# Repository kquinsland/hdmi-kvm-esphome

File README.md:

# `uart_kvm` custom component for ESPHome

This custom component allows for basic control over a generic 8:1 HDMI2.0 KVM switch.
Specifically developed for model number [`PX-UHDKVM801-2.0`](https://www.aliexpress.com/item/1005003927404402.html).

Photos of the internals can be found [on my personal site](https://karlquinsland.com/hdmi-kvm-teardown-and-esphome/).

## Using the component

**Note:** It is possible to get _basic_ control over the KVM without this custom component! ESPHome has _native_ support for _writing_ to a UART. If you only need to tell the KVM what to do then you can use the native [`uart.write`](https://esphome.io/components/uart.html#uart-write-action) call!

However, if  you also want to probe the KVM to get the current active input bank, you will need to _read_ from the UART which can't be done with the native UART component. That's where this custom component comes into play :).

To load this custom component in your ESPHome configuration, you need to use the [`external_components`](https://esphome.io/components/external_components.html) block like so:

```yaml
external_components:
  - source:
      type: git
      url: https://github.com/kquinsland/hdmi-kvm-esphome
    components: [ uart_kvm ]
```

If you have any issues, try to remove the local cache:

```shell
$ rm -rf .esphome/external_components
```

## Example YAML:

This is not a _complete_ YAML file for ESPHome but it does illustrate how to use the custom component and to control the KVM directly with `uart.write` for the various functionalities that the custom component does NOT implement:

```yaml
esphome:
  on_boot:
    priority: 600
    then:
      # Buzzer on is helpful for testing and to know when an automation triggers a change
      - switch.turn_on: sw_tmpl_buzzer
      # I do not want the KVM to automatically switch to any new active HDMI cable
      - switch.turn_off: sw_tmpl_auto_input

# See: https://esphome.io/components/external_components.html
# Will be cached in .esphome/external_components/
##
external_components:
  - source:
      type: git
      url: https://github.com/kquinsland/hdmi-kvm-esphome
    components: [ uart_kvm ]

##
# Expose a dropdown/select to the user via HA
# See: https://esphome.io/components/select/template.html
##
select:
  - platform: template
    id: tmpl_sel_active_port
    name: "Active Bank"
    optimistic: false
    # Create one option for each host the KVM is to control
    # You can use any string you like but the `set_active_bank()` requires an `int` so
    #   choose the strings in the select wisely!
    # Create an entry for each input bank you wish to be able to switch between.
    # E.G.: If you only have 5 hosts attached to an 8 bank switch, you can safely
    #   leave options for 6,7,8 off.
    # In testing the KVM silently ignores commands to switch to an input bank beyond
    #   what the switch supports. E.G.: telling an 8 port KVM to make bank 10 active 
    #    does nothing.
    ##
    options:
      - "1"
      - "2"
      - "3"
      - "4"
      - "5"
      - "6"
      - "7"
      - "8"
    set_action:
      then:
        lambda: |-
          // ESPHome/HA use strings in select components. atoi() fixes this for us :)
          int bank = atoi(x.c_str());
          id(kvm1).set_active_bank(bank);
    # We poll the uart to get the current port
    # Note: ESPHome polls get_active_bank() every several seconds. Unless we actively tell ESPHome to
    #   re-run this lambda as soon as the KVM active input bank changes, this value will lag behind reality
    lambda: |-
      int active = id(kvm1).get_active_bank();
      return to_string(active);

# The initial documentation that the seller provided did not define a way to inquire about buzzer active state or active input chase behavior so we can implement this with standard `uart.write` rather than in custom c++
switch:
  - platform: template
    id: sw_tmpl_buzzer
    name: "${friendly_name_short} Buzzer"
    icon: "mdi:bullhorn"
    entity_category: "config"
    device_class: "switch"
    optimistic: True
    # I don't know how to confirm the state of things so we must assume that sending the "off" command will be enough to turn it off. In testing, sending the "off" command is reliable.
    # If this was not the case, then we could change how things work in HA: instead of a switch
    #   the user will see 2 buttons: one for on, the other for off.
    assumed_state: false
    turn_on_action:
        # Note: the KVM does a short chirp to indicate that it is on
      - uart.write: [0xAA, 0xBB, 0x03, 0x02, 0x01, 0xEE]
    turn_off_action:
      - uart.write: [0xAA, 0xBB, 0x03, 0x02, 0x00, 0xEE]

  - platform: template
    id: sw_tmpl_auto_input
    name: "${friendly_name_short} Auto Input Detection"
    icon: "mdi:bullhorn"
    entity_category: "config"
    device_class: "switch"
    optimistic: True
    assumed_state: False
    turn_on_action:
      - uart.write: [0xAA, 0xBB, 0x03, 0x81, 0x01, 0xEE]
    turn_off_action:
      - uart.write: [0xAA, 0xBB, 0x03, 0x81, 0x00, 0xEE]

uart:
  # We want to impersonate the remote/handset by injecting via the HTX pin which is mapped to 17
  tx_pin: GPIO17
  # Likewise, if the motor controller sends anything to the remote, we _also_ want to hear it.
  rx_pin: GPIO16
  # bog standard 9600 8n1
  baud_rate: 9600

# Load up __init.py__
uart_kvm:
    id: kvm1
    active_bank:
      id: kvm1_bank
      name: "Current Computer"
      # We will expose this to HA through the template select above
      internal: false
      on_value:
        then:
          - lambda: |-
              // Tell ESPHome to refresh the value for the select so it does not lag by several seconds
              id(tmpl_sel_active_port).update();

```

### UART + Component

You will need a TTL <-> RS232 adapter hooked up to an ESP module. I have had a lot of trouble with the cheap MAX232 clone dongles on amazon so you absolutely should do basic loopback tests and confirm signal / voltage levels with an oscilloscope if you are having trouble getting this to work!

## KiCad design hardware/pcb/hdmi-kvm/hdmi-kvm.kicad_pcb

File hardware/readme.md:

# Hardware

The PCB and case are designed to be 1U in height. This also makes it pretty easy to secure to a basic power brick.
The PCB  can be powered via USB or via 12V DC. I wasn't sure if I was going to power the module off of one of the spare USB ports on the KVM or if I wanted to bundle the controller and main power supply so i could have one cable bundle going towards the KVM. I opted for the latter and decided to secure the enclosure to the power supply.

<!-- markdownlint-disable-next-line MD045 -->

The "DC out" cable leaves the enclosure right next to the DB9 port where the serial and power cables are combined with some cable ties before being routed to the KVM on the front of the rack.

## PCB

If you want to edit the pcb, the KiCad 6 files are included subject to [the license terms](../LICENSE.md).

The ESP32 module comes from [this](https://github.com/r0oland/ESP32_mini_KiCad_Library) library. Thanks to [r0oland](https://github.com/r0oland) for that library!

<!-- markdownlint-disable-next-line MD045 -->

### BOM

The PCB is secured to the enclosure with some 4mm M3 screws I had laying around.
The primary components on the PCB are:

- [D1 Mini style ESP32 chip](https://www.aliexpress.com/item/2251832633593063.html)
- [Configurable DC Buck converter module](https://www.aliexpress.com/item/32833398811.html). This steps the 12V dc from the KVM power supply down to the 5V for the ESP32 module.
- [Ultra Compact RS232 to TTL Converter with Female DB9 (3.3V to 5V)](https://www.amazon.com/gp/product/B00OPTOKI0/)

#### gerber

If you want to make zero changes, the [gerber files are included](./pcb/hdmi-kvm/export/2022.04.23.zip) and are subject to [the license terms](../LICENSE.md).

The gerber files / KiCad project are set up for use with JLCPCB but probably would work as-is with other PCB fab houses, too.

## Enclosure

It's not my best work but it works. I printed with my "fast, not accurate" profile so the snaps that are meant to keep the lid attached to the rest of the body don't work that well; this is the reason for the white tape in the picture.

You should be OK if you print slower but STEP files for both the [PCB](./pcb/hdmi-kvm/hdmi-kvm.step) and [enclosure](./enclosure/kvm-controller-enclosure.step) are included - subject to [the license terms](../LICENSE.md),

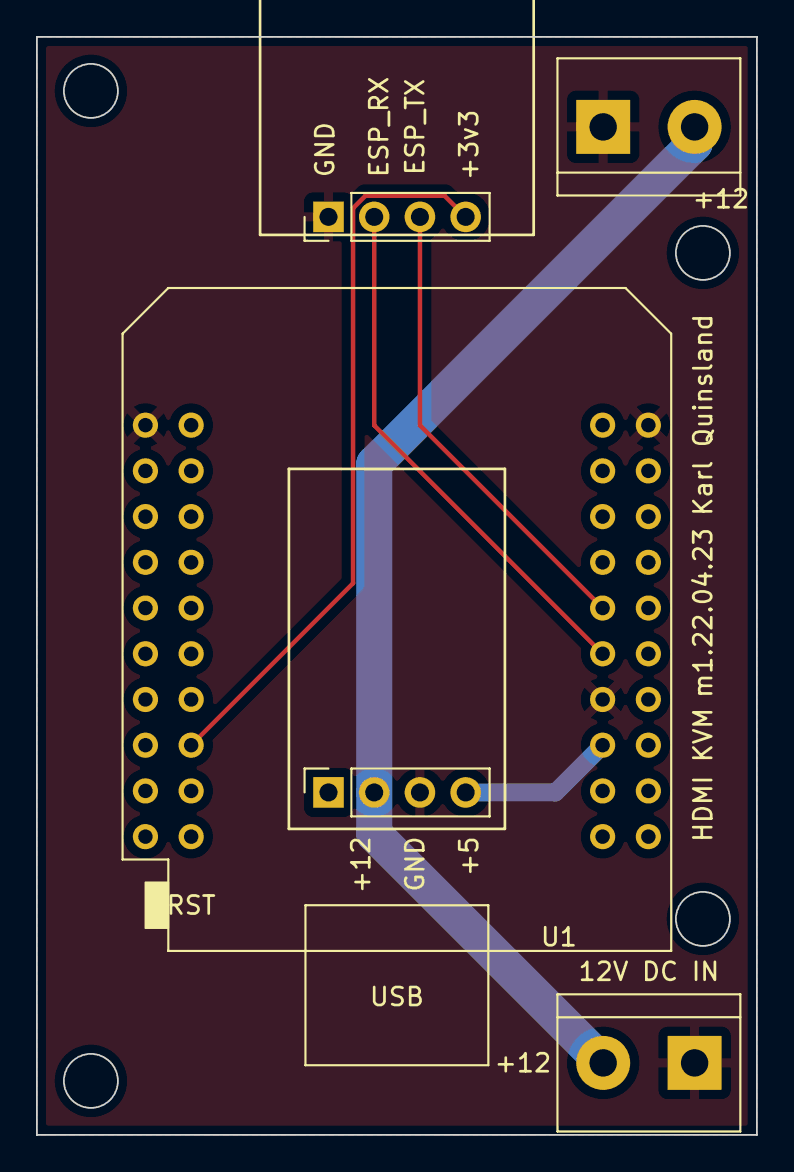
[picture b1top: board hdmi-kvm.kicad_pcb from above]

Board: 2 copper layers, 40.0 x 61.0 mm, 5 parts (0 on the bottom side), 6 nets.

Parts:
J1: 12V DC IN; TerminalBlock_bornier-2_P5.08mm
J2: 12V DC OUT; TerminalBlock_bornier-2_P5.08mm
J3: DC_BUCK_CONN; PinSocket_1x04_P2.54mm_Vertical
J4: Conn_01x04_Male; PinHeader_1x04_P2.54mm_Vertical
U1: mini_esp32; ESP32_mini

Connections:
+3V3: J4.4, U1.16 (3V3)
+5V: J3.4, U1.35 (VCC_(USB))
+12V: J1.2, J2.2, J3.2
ESP_RX: J4.2, U1.31 (IO_16/D4)
ESP_TX: J4.3, U1.29 (IO_17/D3)
GND: J1.1, J2.1, J3.3, J4.1, U1.1 (GND), U1.22 (GND), U1.33 (GND)

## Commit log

2022-04-15 Initial commit
    Includes functional `probe.py` and docs from seller / found on the web
    Basic custom component passes initial esphome validation but does not yet compile
2022-04-16 Working compile
    lots of WARN, still... but it compiles and links.
2022-04-16 Add more docs / windows program from the seller
2022-04-16 more progress on the custom component
    But I still need to refactor it. This is the commit before I do that.
2022-04-16 More reliable polling implementation
    It was a lot of work to figure out how to filter the UART
    Now, the only problem is that I am not called often enough and there's too much noise on the UART so it takes ~10s / 2 calls before I get back packets that I expect.
    It might be worth going BACK to loop() as I can then send the "what active port?" message quickly...
2022-04-16 Working
    I have everything working as expected / desired!
2022-04-17 added datasheets
2022-04-17 added some notes about docs
    cleaned up file paths a bit, added datasheets for most of the ICs that I could find
2022-04-17 small cleanup
2022-04-17 remove dupe readme files
2022-04-17 remove remnants of PollingComponent implementation
    remove misc notes / some cleanup
2022-04-17 rename things to work for ESPHome remote
2022-04-17 Add datasheet
2022-04-17 remove buzzer_state function from header
    removed it from Cpp, didn't remove it from header
2022-04-17 Tweak the readme
    includes a commented example yaml showing how to get the active bank via sensor and integrate with HA using select functions.
    Some basic functionality was removed from custom component and implemented with basic uart.write
2022-04-17 add example image from HA
2022-05-14 Add hardware documentation
    Misc spelling / linting
    License
    STEP/GERBER files and example images added
2025-07-04 Add renovate.json
